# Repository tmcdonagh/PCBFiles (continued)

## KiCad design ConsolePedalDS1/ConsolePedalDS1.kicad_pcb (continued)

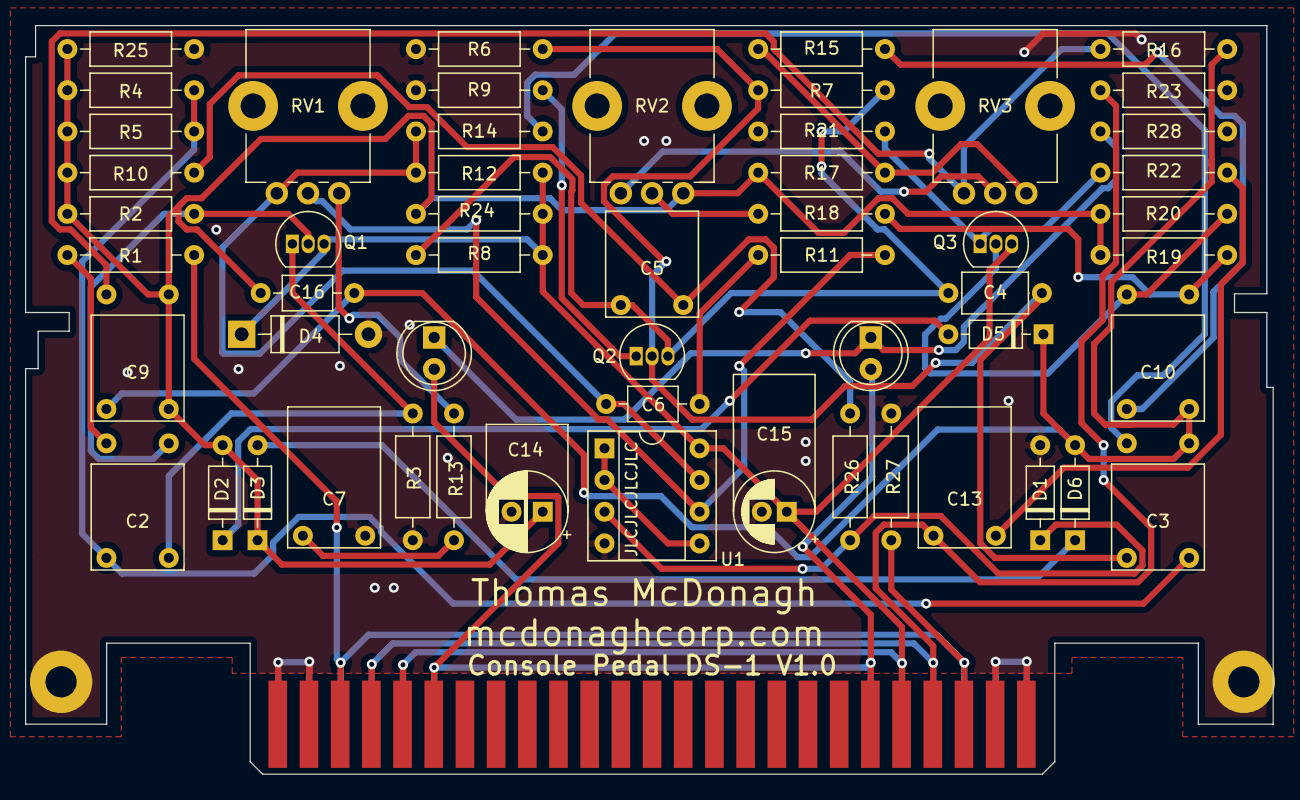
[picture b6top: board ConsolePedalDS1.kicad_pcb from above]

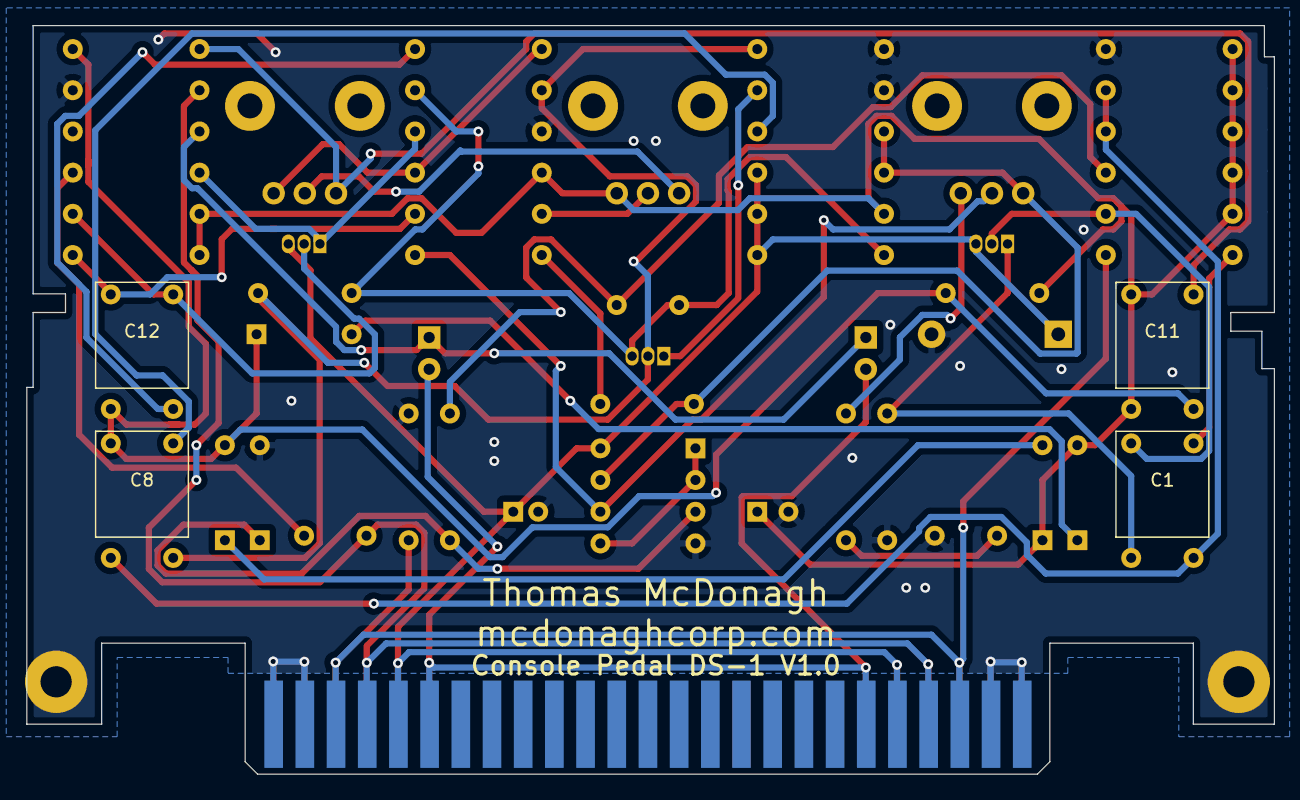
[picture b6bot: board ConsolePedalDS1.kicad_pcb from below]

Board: 2 copper layers, 100.0 x 60.0 mm, 62 parts (4 on the bottom side), 35 nets.

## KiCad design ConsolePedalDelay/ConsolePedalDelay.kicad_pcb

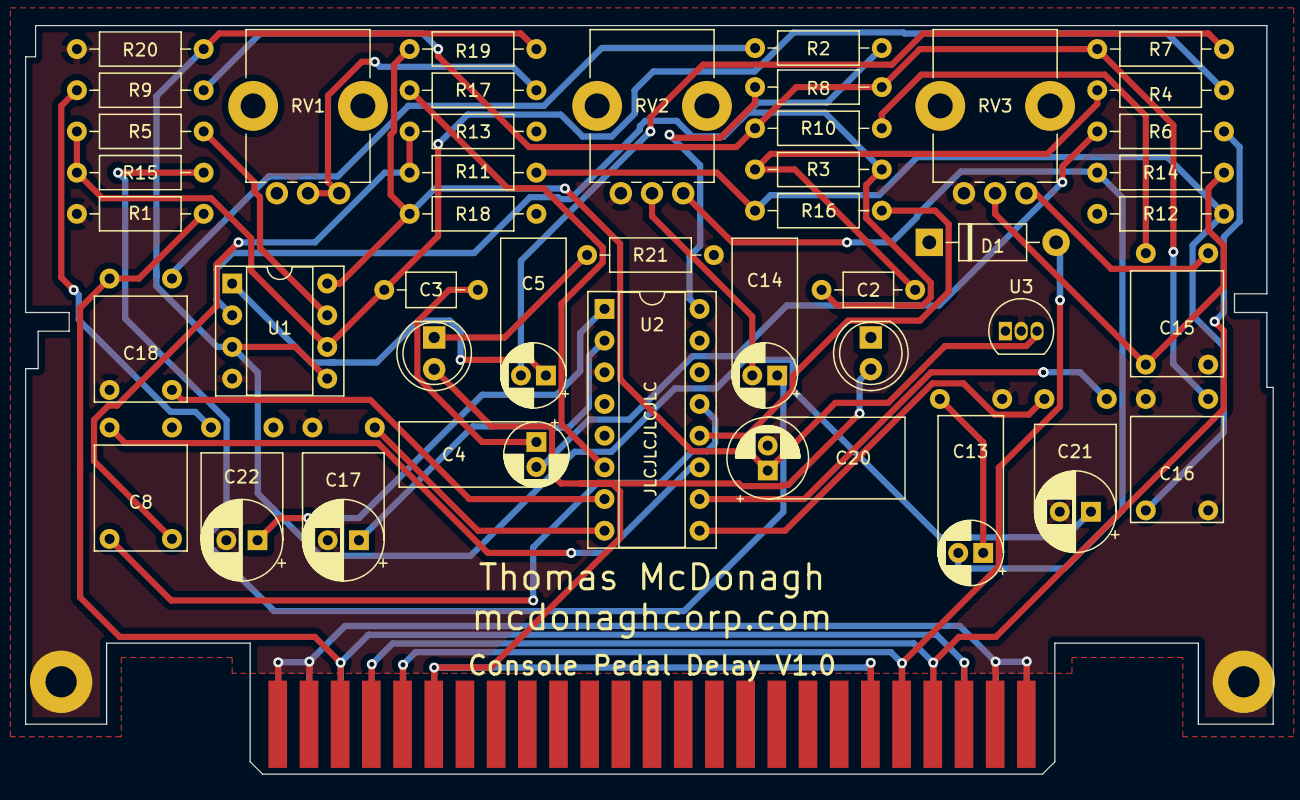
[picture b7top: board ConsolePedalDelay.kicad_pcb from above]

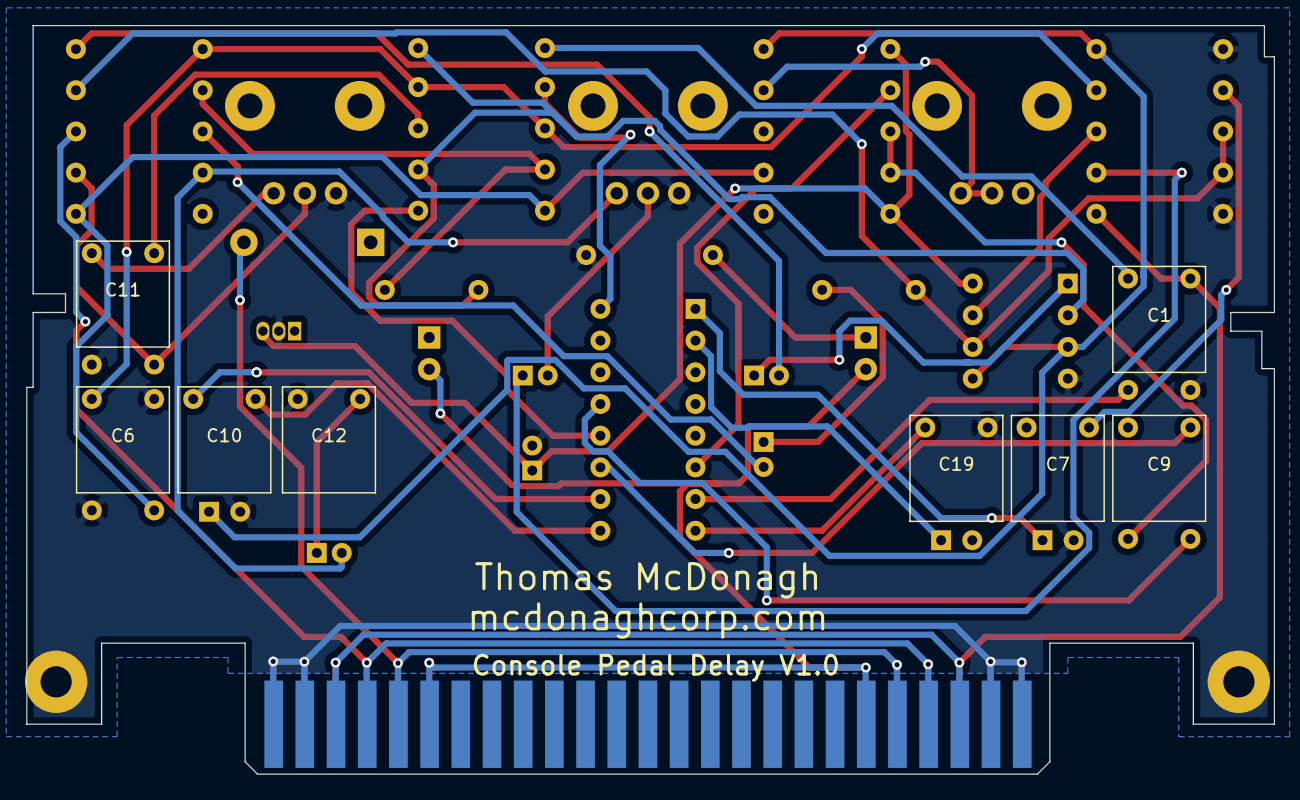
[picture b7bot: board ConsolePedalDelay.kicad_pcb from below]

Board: 2 copper layers, 100.0 x 60.0 mm, 55 parts (8 on the bottom side), 40 nets.

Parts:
C1, C11: 22nF; C_Flat_L7.2_H6.5
C2: 47pF; C_Axial_L3.8mm_D2.6mm_P7.50mm_Horizontal
C3: 100pF; C_Axial_L3.8mm_D2.6mm_P7.50mm_Horizontal
C4, C5, C13, C14: 1uF; CP_Radial_D5.0mm_P2.00mm_L11.0mm
C6: 4.7nF; C_Flat_L7.2_H6.5
C7, C8: 2.2nF; C_Flat_L7.2_H6.5
C9, C10, C18, C19: 100nF; C_Flat_L7.2_H6.5
C12: 10nF; C_Flat_L7.2_H6.5
C15: 47nF; C_Flat_L7.2_H6.5
C16: 15nF; C_Flat_L7.2_H6.5
C17, C21, C22: 47uF; CP_Radial_D6.3mm_P2.50mm_L7.0mm
C20: 100uF; CP_Radial_D6.3mm_P2.00mm_L11.0mm
D1: 1N5817; D_DO-41_SOD81_P10.16mm_Horizontal
D2, D3: LED; LED_D5.0mm
H1, H2: MountingHole_Pad; MountingHole_2.5mm_Pad
J1: Conn_02x25_Counter_Clockwise; N64-Connector
R1: 1M; R_Axial_DIN0207_L6.3mm_D2.5mm_P10.16mm_Horizontal
R2: 180K; R_Axial_DIN0207_L6.3mm_D2.5mm_P10.16mm_Horizontal
R3: 360K; R_Axial_DIN0207_L6.3mm_D2.5mm_P10.16mm_Horizontal
R4: 22K; R_Axial_DIN0207_L6.3mm_D2.5mm_P10.16mm_Horizontal
R5: 12K; R_Axial_DIN0207_L6.3mm_D2.5mm_P10.16mm_Horizontal
R6, R13: 1K; R_Axial_DIN0207_L6.3mm_D2.5mm_P10.16mm_Horizontal
R7, R8, R9, R12, R16, R19, R20: 10K; R_Axial_DIN0207_L6.3mm_D2.5mm_P10.16mm_Horizontal
R10: 5.1K; R_Axial_DIN0207_L6.3mm_D2.5mm_P10.16mm_Horizontal
R11, R15: 20K; R_Axial_DIN0207_L6.3mm_D2.5mm_P10.16mm_Horizontal
R14: 2K; R_Axial_DIN0207_L6.3mm_D2.5mm_P10.16mm_Horizontal
R17: 2.2K; R_Axial_DIN0207_L6.3mm_D2.5mm_P10.16mm_Horizontal
R18: 33; R_Axial_DIN0207_L6.3mm_D2.5mm_P10.16mm_Horizontal
R21: 100K; R_Axial_DIN0207_L6.3mm_D2.5mm_P10.16mm_Horizontal
RV1: Delay 50KB; Potentiometer_Bourns_PTV09A-1_Single_Vertical
RV2: Level 50KB; Potentiometer_Bourns_PTV09A-1_Single_Vertical
RV3: Repeat 50KB; Potentiometer_Bourns_PTV09A-1_Single_Vertical
U1: TL072; DIP-8_W7.62mm_Socket
U2: PT2399; DIP-16_W7.62mm_Socket
U3: L78L05_TO92; TO-92_Inline

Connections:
+9V: D1.2, J1.5, J1.21, J1.30, J1.46
/5V: C22.1, U2.1, U3.1
/Input: C1.2, J1.3, J1.23, J1.28, J1.48, R1.2
/LEDPower: D2.2, D3.2, J1.6, J1.20, J1.31, J1.45
/Output: J1.4, J1.22, J1.29, J1.47, R6.2
/VREF: C21.1, R19.2, R20.1, U1.3, U1.5
/pin2: C17.1, U2.2
/pin4: RV1.3, U2.4
/pin6: R17.1, U2.6
/pin7: C18.1, U2.7
/pin8: C19.1, U2.8
/pin9: C10.2, U2.9
/pin10: C10.1, U2.10
/pin11: C9.2, U2.11
/pin12: C9.1, R16.2, U2.12
/pin13: C8.2, R12.1, U2.13
/pin14: C8.1, R11.1, R13.1, U2.14
/pin15: C7.2, R9.2, U2.15
/pin16: C7.1, R8.1, U2.16
GND: C6.2, C12.1, C15.1, C16.1, C17.2, C18.2, C19.2, C20.2, C21.2, C22.2, H1.1, H2.1, J1.1, J1.2, J1.24, J1.25, J1.26, J1.27, J1.49, J1.50, R1.1, R20.2, R21.1, RV2.3, RV3.3, U1.4, U2.3, U3.2
unnamed: C1.1, R2.1
unnamed: C2.1, R2.2, R3.2, U1.2
unnamed: C2.2, C5.1, R3.1, R4.1, U1.1
unnamed: C3.1, R4.2, R5.1, R15.1, U1.6
unnamed: C3.2, C4.1, R5.2, U1.7
unnamed: C4.2, R6.1
unnamed: C5.2, R7.2
unnamed: C6.1, R7.1, R8.2, R9.1, R10.1
unnamed: C11.1, RV3.1
unnamed: C11.2, R10.2
unnamed: C12.2, C13.1, R13.2
unnamed: C13.2, R14.1, RV2.1
unnamed: C14.1, R15.2
unnamed: C14.2, RV2.2
unnamed: C15.2, R14.2, RV3.2
unnamed: C16.2, R11.2, R12.2, R16.1
unnamed: C20.1, R18.1, R19.1, U1.8, U3.3
unnamed: D1.1, R18.2
unnamed: D2.1, D3.1, R21.2
unnamed: R17.2, RV1.1, RV1.2

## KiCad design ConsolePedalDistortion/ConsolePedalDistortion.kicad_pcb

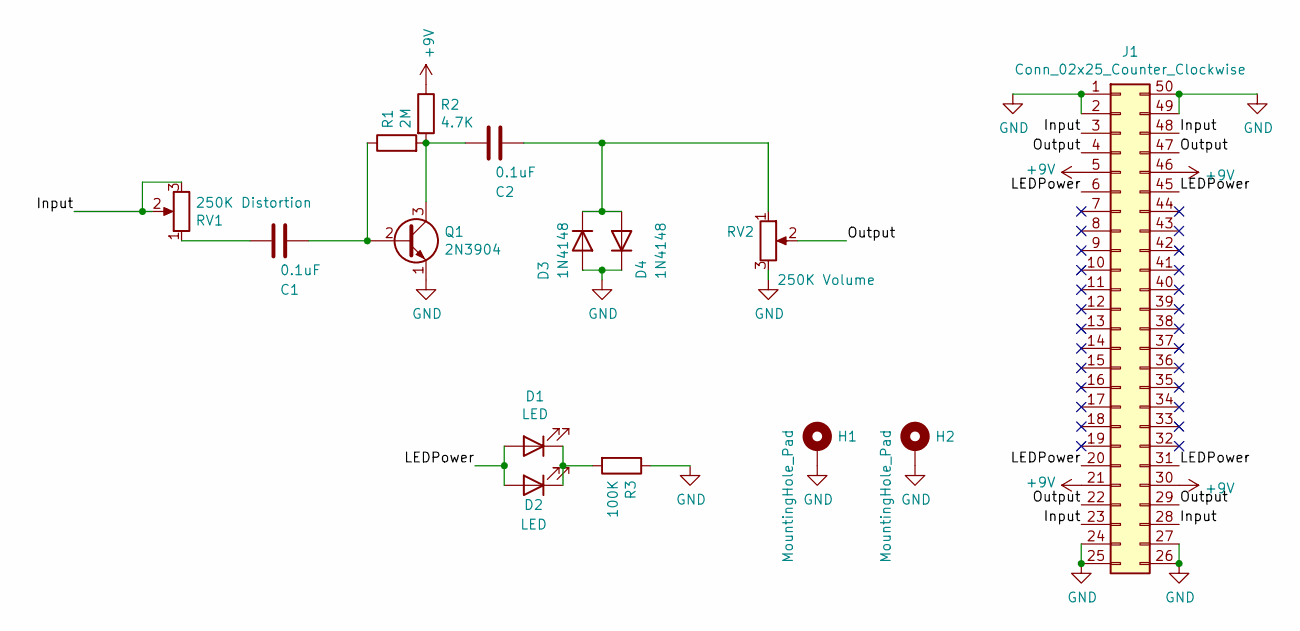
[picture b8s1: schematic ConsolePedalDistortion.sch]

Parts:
C1, C2: 0.1uF; C_Disc_D10.5mm_W5.0mm_P7.50mm
D1, D2: LED; LED_D5.0mm
D3, D4: 1N4148; D_DO-35_SOD27_P7.62mm_Horizontal
H1, H2: MountingHole_Pad; MountingHole_2.5mm_Pad
J1: Conn_02x25_Counter_Clockwise; N64-Connector
Q1: 2N3904; TO-92_Inline
R1: 2M; R_Axial_DIN0207_L6.3mm_D2.5mm_P10.16mm_Horizontal
R2: 4.7K; R_Axial_DIN0207_L6.3mm_D2.5mm_P10.16mm_Horizontal
R3: 100K; R_Axial_DIN0207_L6.3mm_D2.5mm_P10.16mm_Horizontal
RV1: 250K Distortion; Potentiometer_Bourns_PTV09A-1_Single_Vertical
RV2: 250K Volume; Potentiometer_Bourns_PTV09A-1_Single_Vertical

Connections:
+9V: J1.5, J1.21, J1.30, J1.46, R2.1
/Input: J1.3, J1.23, J1.28, J1.48, RV1.2, RV1.3
/LEDPower: D1.2 (A), D2.2 (A), J1.6, J1.20, J1.31, J1.45
/Output: J1.4, J1.22, J1.29, J1.47, RV2.2
GND: D3.2 (A), D4.1 (K), H1.1, H2.1, J1.1, J1.2, J1.24, J1.25, J1.26, J1.27, J1.49, J1.50, Q1.1 (E), R3.1, RV2.3
unnamed: C1.1, Q1.2 (B), R1.1
unnamed: C1.2, RV1.1
unnamed: C2.1, D3.1 (K), D4.2 (A), RV2.1
unnamed: C2.2, Q1.3 (C), R1.2, R2.2
unnamed: D1.1 (K), D2.1 (K), R3.2

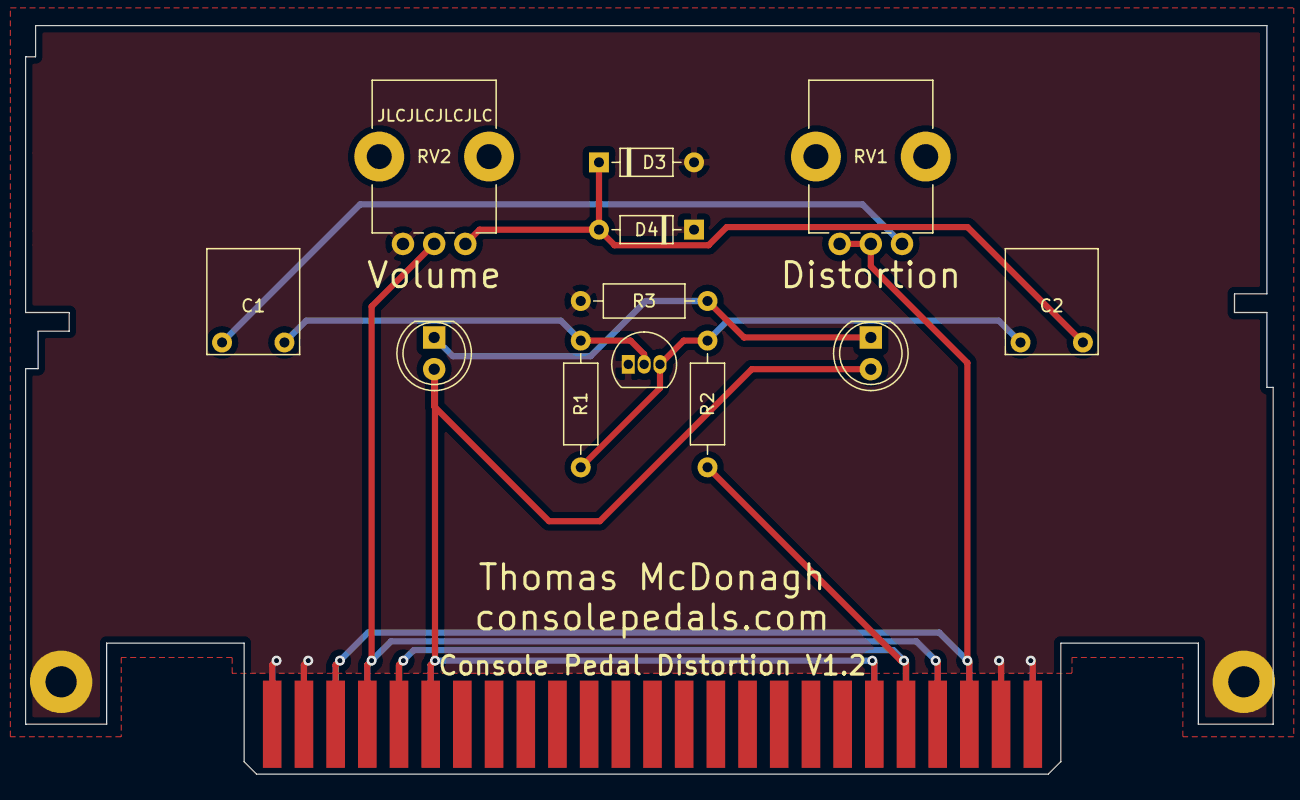
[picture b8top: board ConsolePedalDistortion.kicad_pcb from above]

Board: 2 copper layers, 100.0 x 60.0 mm, 15 parts (0 on the bottom side), 10 nets.

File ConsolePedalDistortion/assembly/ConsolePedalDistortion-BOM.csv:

Value,Designator,Footprint,LCSC Part #,
100nF,"C1,C2",0603,C14663,
1N914,"D3,D4",SOD-323F,C258181,
2N3904,Q1,SOT-23-3,C18536,
2M,R1,0603,C22976,
4.7K,R2,0603,C23162,
100K,R3,0603,C25803,
,,,,
,,,,
,,,,
,,,,
,,,,
,,,,
